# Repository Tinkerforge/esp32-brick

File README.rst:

ESP32 Brick
===========

This repository contains the firmware source code and the hardware design
files. The documentation generator configs can be found at
https://github.com/Tinkerforge/generators

Repository Overview
-------------------

.. DO NOT EDIT THIS OVERVIEW MANUALLY! CHANGE https://github.com/Tinkerforge/esp32-firmware/repo_overview.rst AND COPY THAT BLOCK INTO ALL REPOS LISTED BELOW. TODO: AUTOMATE THIS

Software
~~~~~~~~
- `esp32-firmware <https://github.com/Tinkerforge/esp32-firmware>`__  **Please report any issues concerning WARP hard- and software here!** Source code of the ESP32 firmware shared between all WARP Chargers and Energy Managers

- `tfjson <https://github.com/Tinkerforge/tfjson>`__ SAX style JSON serializer and deserializer
- `tfmodbustcp <https://github.com/Tinkerforge/tfmodbustcp>`__ Modbus TCP server and client implementation
- `tfocpp <https://github.com/Tinkerforge/tfocpp>`__ OCPP 1.6 implementation
- `tftools <https://github.com/Tinkerforge/tftools>`__ Miscellaneous tools and helpers

- `esp32-remote-access <https://github.com/Tinkerforge/esp32-remote-access>`__ Source code of the my.warp-charger.com remote access server

- `warp-charger <https://github.com/Tinkerforge/warp-charger>`__ The source code of (docs.)warp-charger.com and the printed manual, released firmwares, datasheets and documents, as well as some tools and hardware design files
- `api.warp-charger.com <https://github.com/Tinkerforge/api.warp-charger.com>`__ Serves APIs that are used by WARP Chargers to obtain relevant public information like day ahead prices
- `vislog.warp-charger.com <https://github.com/Tinkerforge/vislog.warp-charger.com>`__ Visualizes WARP Charger logs and EVSE debug protocols
- `dbus-warp-charger <https://github.com/Tinkerforge/dbus-warp-charger>`__ Integrates WARP Chargers into a Victron Energy Venus OS device (e.g. Cerbo GX)

WARP Charger Hardware
~~~~~~~~~~~~~~~~~~~~~~

- `esp32-brick <https://github.com/Tinkerforge/esp32-brick>`__ Hardware design files of the ESP32 Brick
- `evse-bricklet <https://github.com/Tinkerforge/evse-bricklet>`__  Firmware source code and hardware design files of the EVSE Bricklet
- `rs485-bricklet <https://github.com/Tinkerforge/rs485-bricklet>`__ Firmware source code and hardware design files of the RS485 Bricklet

WARP2 Charger Hardware
~~~~~~~~~~~~~~~~~~~~~~

- `esp32-ethernet-brick <https://github.com/Tinkerforge/esp32-ethernet-brick>`__ Hardware design files of the ESP32 Ethernet Brick
- `evse-v2-bricklet <https://github.com/Tinkerforge/evse-v2-bricklet>`__ Firmware source code and hardware design files of the EVSE 2.0 Bricklet
- `nfc-bricklet <https://github.com/Tinkerforge/nfc-bricklet>`__ Firmware source code and hardware design files of the NFC Bricklet

WARP3 Charger Hardware
~~~~~~~~~~~~~~~~~~~~~~

- `warp-esp32-ethernet-brick <https://github.com/Tinkerforge/warp-esp32-ethernet-brick>`__ Hardware design files of the WARP ESP32 Ethernet Brick
- `evse-v3-bricklet <https://github.com/Tinkerforge/evse-v3-bricklet>`__ Firmware source code and hardware design files of the EVSE 3.0 Bricklet
- `nfc-bricklet <https://github.com/Tinkerforge/nfc-bricklet>`__ Firmware source code and hardware design files of the NFC Bricklet

WARP Energy Manager Hardware
~~~~~~~~~~~~~~~~~~~~~~~~~~~~

- `esp32-ethernet-brick <https://github.com/Tinkerforge/esp32-ethernet-brick>`__ Hardware design files of the ESP32 Ethernet Brick
- `warp-energy-manager-bricklet <https://github.com/Tinkerforge/warp-energy-manager-bricklet>`__ Firmware source code and hardware design files of the WARP Energy Manager Bricklet

WARP Energy Manager 2.0 Hardware
~~~~~~~~~~~~~~~~~~~~~~~~~~~~~~~~

- `esp32-ethernet-brick <https://github.com/Tinkerforge/esp32-ethernet-brick>`__ Hardware design files of the ESP32 Ethernet Brick
- `warp-energy-manager-v2-bricklet <https://github.com/Tinkerforge/warp-energy-manager-v2-bricklet>`__ Firmware source code and hardware design files of the WARP Energy Manager 2.0 Bricklet
- `warp-front-panel-bricklet <https://github.com/Tinkerforge/warp-front-panel-bricklet>`__ Firmware source code and hardware design files of the WARP Front Panel Bricklet

Forked/patched projects
~~~~~~~~~~~~~~~~~~~~~~~

- `arduino-esp32 <https://github.com/Tinkerforge/arduino-esp32>`__
- `esp32-arduino-libs <https://github.com/Tinkerforge/esp32-arduino-libs>`__
- `WireGuard-ESP32-Arduino <https://github.com/Tinkerforge/WireGuard-ESP32-Arduino>`__

Repository Content
------------------

software/:
 * examples/: Examples for all supported languages
 * build/: Compiled files
 * src/: Source code of firmware
 * Makefile: Makefile to build project

hardware/:
 * Contains KiCad project files and additionally schematics as PDF

datasheets/:
 * Contains datasheets for sensors and complex ICs that are used

Hardware
--------

The hardware is designed with the open source EDA Suite KiCad
(http://www.kicad.org). Before you are able to open the files,
you have to install the Tinkerforge kicad-libraries
(https://github.com/Tinkerforge/kicad-libraries). You can either clone
them directly in hardware/ or clone them in a separate folder and
symlink them into hardware/
(ln -s kicad_path/kicad-libraries project_path/hardware). After that you
can open the .pro file in hardware/ with KiCad and from there view and
modify the schematics and the PCB layout.

Software
--------

See README.txt in the software folder for details.

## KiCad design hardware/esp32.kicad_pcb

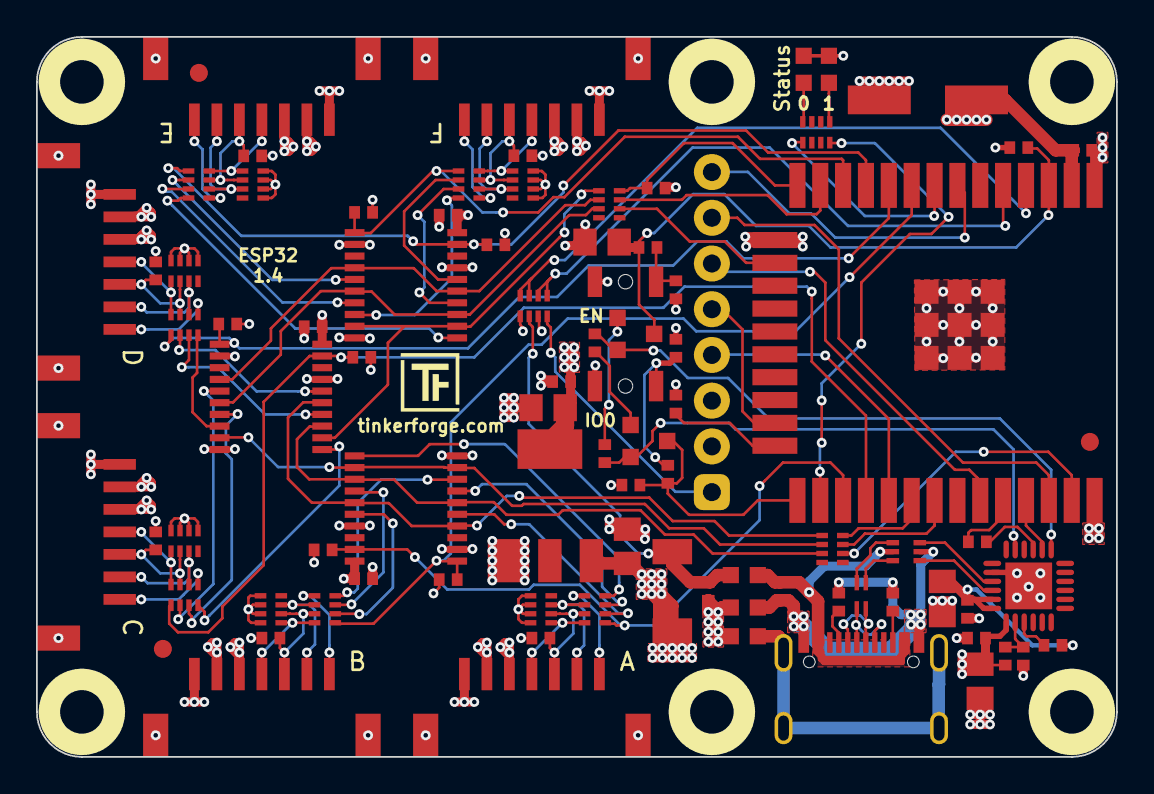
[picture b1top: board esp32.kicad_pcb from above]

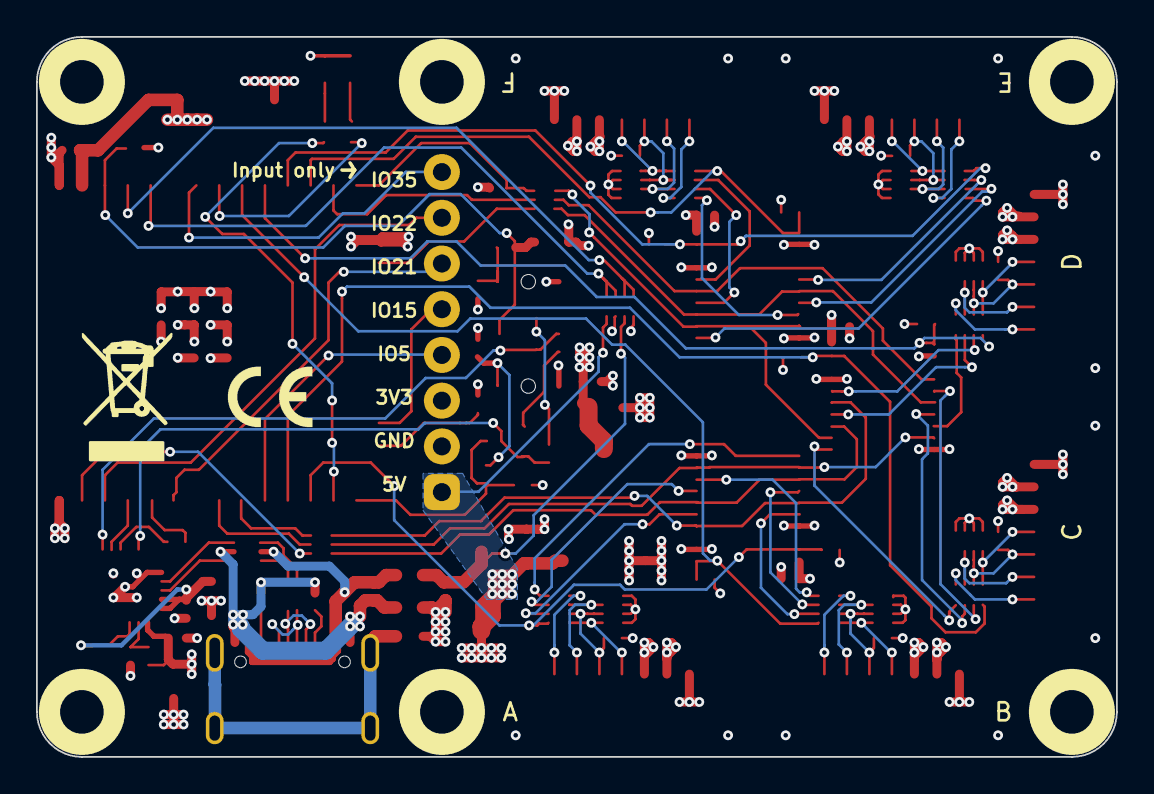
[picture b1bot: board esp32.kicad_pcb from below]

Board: 4 copper layers, 60.0 x 40.0 mm, 94 parts (2 on the bottom side), 101 nets.

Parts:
C101, C102: 1uF; C0402F
C103, C104, C108, C111: 4.7uF; C0805E
C105: 100uF; ELKO_63
C106, C107, C109, C110, C201, C202, C203: 100nF; C0402F
C112: 10µF; C0805E
C113, C114: 1nF; C0402F
CP201, CP202, CP203, CP204, CP205, CP206: 220pF; 4X0402
D101: blue; D0603F
D102: PMEG4050; SOD-128
D105: green; D0603F
F101, F102, F103, F104: DRILL; DRILL_NP
Fiducial_Mark: VAL**; Fiducial_Mark
Fiducial_Mark#2, Fiducial_Mark#3: VAL**; Fiducial_Mark
J101: USB-C-2
L101, L103, L104: FB; R0603F
L102: 744230900; WE-CNSW-0603
P101: EXT_HEADER; pin_array_1x8-P2mm_D1mm
P201, P202, P203, P204, P205, P206: CON-SENSOR2
Q101, Q102: BC817; SOT23EBC
R1, R2, R3, R4, R108, R109, R201, R202: 100k; R0402F
R101, R103: 5.1k; R0402F
R102, R112: DNP; R0402F
R104: 22k; R0402F
R105: 47k; R0402F
R106: 1k; R0402F
R107: 100; R0402F
R110, R111: 12k; R0402F
R113, R114: 470; R0402F
R203, R204, R205, R206, R207, R208: 10k; R0402F
RP101, RP102, RP201, RP202, RP203, RP204, RP205, RP206: 82; 4X0402
RP104, RP105: 1k; 4X0402
SW101, SW102: B3U-1000P
U101: 82400152; SOT563-SPEC
U102: AZ1117E-3.3V; SOT-223
U103: CP2102N-A02-GQFN24R; QFN24-4x4mm-0.5mm
U104: ESP32WRM32E128PH; ESP32-WROOM-32
U201, U202, U203: 74AHC244; TSSOP20
VAL: WEEE_7mm
VAL#2: CE_5mm

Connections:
3V3: C105.1, C106.2, C108.2, C109.2, C201.2, C202.2, C203.2, D101.1, D105.1, P101.3, P201.3, P202.3, P203.3, P204.3, P205.3, P206.3, R1.1, R2.1, R3.1, R4.1, R110.2, R111.1, R201.1, R202.1, R203.1, R204.1, R205.1, R206.1, R207.1, R208.1, U102.2, U104.2, U201.20, U202.20, U203.20
5V: C103.2, C104.2, C107.2, D102.2, P101.1, P201.1, P202.1, P203.1, P204.1, P205.1, P206.1, R104.2, RP104.8, U102.3, U103.7
B0-CLK: RP101.2, U201.4, U201.15, U202.4
B0-CS0: R203.2, RP201.1, U104.12, U201.1
B0-CS1: R205.2, RP202.1, U104.11, U201.19
B0-CS2: R204.2, RP203.1, U104.10, U202.1
B0-MISO: RP101.1, U201.9, U201.12, U202.12
B0-MOSI: RP101.3, U201.6, U201.13, U202.6
B1-CLK: RP102.1, U202.15, U203.4, U203.15
B1-CS0: R206.2, RP204.1, U104.28, U202.19
B1-CS1: R207.2, RP205.1, U104.9, U203.1
B1-CS2: R208.2, RP206.1, U104.27, U203.19
B1-MISO: RP102.2, U202.9, U203.9, U203.12
B1-MOSI: RP102.3, U202.13, U203.6, U203.13
ESP_ADC_5V: RP104.3, RP104.4, U104.4
ESP_ADC_VUSB: RP104.1, RP104.2, U104.5
ESP_EN: C112.2, Q101.C, R111.2, R113.2, U104.3
ESP_IO0: Q102.C, R110.1, R114.2, U104.25
ESP_IO2: R112.1, U104.24
ESP_IO5: P101.4, U104.29
ESP_IO15: P101.5, U104.23
ESP_IO21: P101.6, U104.33
ESP_IO22: P101.7, U104.36
ESP_IO35: P101.8, U104.7
ESP_RXD: R107.2, U104.34
ESP_TXD: U103.20, U104.35
GND: C101.1, C103.1, C104.1, C105.2, C106.1, C107.1, C108.1, C109.1, C110.1, C111.1, C112.1, C113.2, C114.2, C201.1, C202.1, C203.1, CP201.5, CP201.6, CP201.7, CP201.8, CP202.5, CP202.6, CP202.7, CP202.8, CP203.5, CP203.6, CP203.7, CP203.8, CP204.5, CP204.6, CP204.7, CP204.8, CP205.5, CP205.6, CP205.7, CP205.8, CP206.5, CP206.6, CP206.7, CP206.8, L101.1, L104.2, P101.2, P201.2, P201.EP, P202.2, P202.EP, P203.2, P203.EP, P204.2, P204.EP, P205.2, P205.EP, P206.2, P206.EP, R102.2, R105.1, R112.2, RP104.5, RP104.7, SW101.1, SW102.1, U102.1, U103.2, U103.EXP, U104.1, U104.15, U104.38, U104.39, U201.2, U201.10, U201.17, U202.2, U202.10, U202.17, U203.2, U203.10, U203.17
LED_BLUE: RP105.5, U104.8
LED_GREEN: RP105.8, U104.26
unnamed: C101.2, D102.1, L103.2, RP104.6
unnamed: C110.2, C111.2, R106.2, U103.5, U103.6
unnamed: C113.1, R113.1, SW101.2
unnamed: C114.1, R114.1, SW102.2
unnamed: CP201.1, P201.4, RP201.8
unnamed: CP201.2, P201.5, R1.2, RP201.7
unnamed: CP201.3, P201.6, RP201.6
unnamed: CP202.1, P202.4, RP202.8
unnamed: CP202.2, P202.5, R2.2, RP202.7
unnamed: CP202.3, P202.6, RP202.6
unnamed: CP203.1, P203.4, RP203.8
unnamed: CP203.2, P203.5, R3.2, RP203.7
unnamed: CP203.3, P203.6, RP203.6
unnamed: CP204.1, P204.4, RP204.8
unnamed: CP204.2, P204.5, R4.2, RP204.7
unnamed: CP204.3, P204.6, RP204.6
unnamed: CP205.1, P205.4, RP205.8
unnamed: CP205.2, P205.5, R201.2, RP205.7
unnamed: CP205.3, P205.6, RP205.6
unnamed: CP206.1, P206.4, RP206.8
unnamed: CP206.2, P206.5, R202.2, RP206.7
unnamed: CP206.3, P206.6, RP206.6
unnamed: D101.2, RP105.4
unnamed: D105.2, RP105.1
unnamed: J101.2, L102.2
unnamed: J101.3, L102.3
unnamed: J101.4, R101.2
unnamed: J101.5, R103.2
unnamed: J101.SHD, L101.2
unnamed: L102.1, U101.6
unnamed: L102.4, U101.4
unnamed: P201.7, RP201.5
unnamed: P202.7, RP202.5
unnamed: P203.7, RP203.5
unnamed: P204.7, RP204.5
unnamed: P205.7, RP205.5
unnamed: P206.7, RP206.5
unnamed: Q101.B, R108.2
unnamed: Q101.E, R109.1, U103.19
unnamed: Q102.B, R109.2
unnamed: Q102.E, R108.1, U103.23
unnamed: R102.1, RP101.8, U104.14
unnamed: R104.1, R105.2, U103.8
unnamed: R106.1, U103.9
unnamed: R107.1, U103.21
unnamed: RP101.6, U104.16
unnamed: RP101.7, U104.13
unnamed: RP102.6, U104.37
unnamed: RP102.7, U104.31
unnamed: RP102.8, U104.30
unnamed: RP201.2, U201.16
unnamed: RP201.3, U201.14
unnamed: RP201.4, U201.8
unnamed: RP202.2, U201.5
unnamed: RP202.3, U201.7
unnamed: RP202.4, U201.11
unnamed: RP203.2, U202.16
unnamed: RP203.3, U202.14
unnamed: RP203.4, U202.8
unnamed: RP204.2, U202.5
unnamed: RP204.3, U202.7
unnamed: RP204.4, U202.11
unnamed: RP205.2, U203.16
unnamed: RP205.3, U203.14
unnamed: RP205.4, U203.8
unnamed: RP206.2, U203.5
unnamed: RP206.3, U203.7
unnamed: RP206.4, U203.11
unnamed: U101.1, U103.4
unnamed: U101.3, U103.3
USB_5V: C102.2, J101.1, L103.1, U101.5
USB_GND: C102.1, J101.6, L104.1, R101.1, R103.1, U101.2

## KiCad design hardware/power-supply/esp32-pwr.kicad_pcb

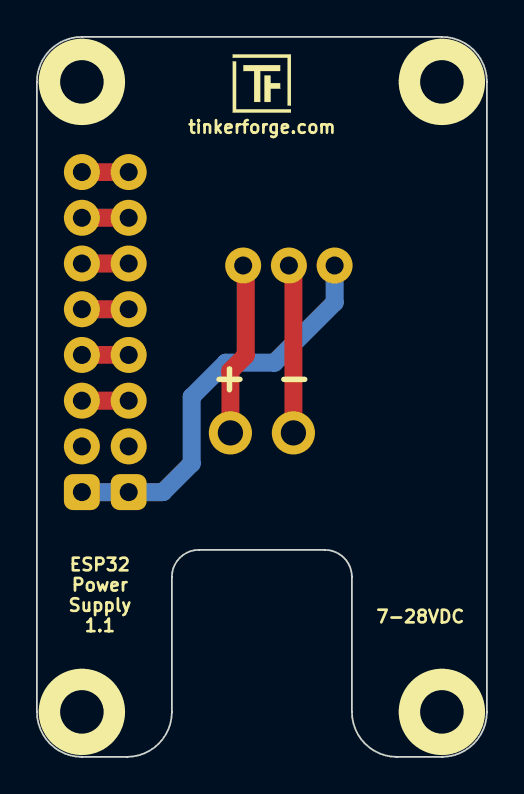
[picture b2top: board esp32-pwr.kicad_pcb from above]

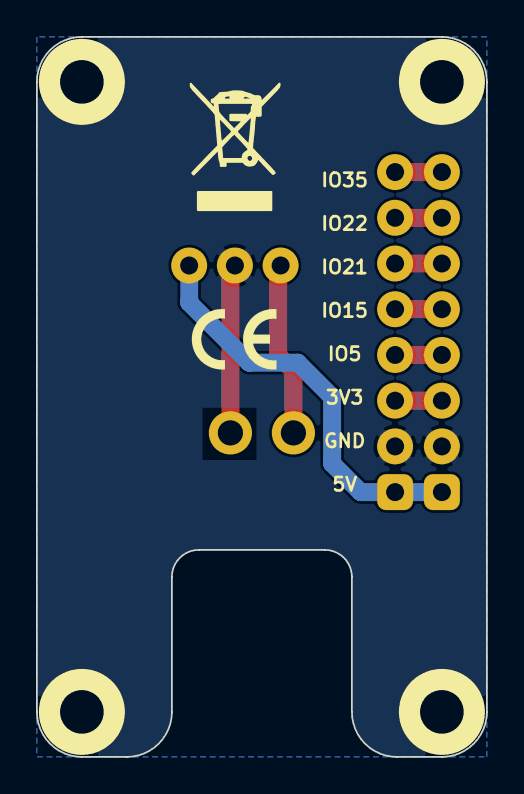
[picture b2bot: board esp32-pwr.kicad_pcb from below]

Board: 2 copper layers, 25.0 x 40.0 mm, 8 parts (2 on the bottom side), 9 nets.

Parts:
F103, F104: DRILL; DRILL_NP
P101, P103: EXT_HEADER; pin_array_1x8-P2mm_D1mm
P102: PWR IN; OQ_2P
U101: WPMDL1100501S; WPMDL110
VAL: CE_5mm
VAL#2: WEEE_7mm

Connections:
5V: P101.1, P103.1, U101.3
GND: P101.2, P102.2, P103.2, U101.2
unnamed: P101.3, P103.3
unnamed: P101.4, P103.4
unnamed: P101.5, P103.5
unnamed: P101.6, P103.6
unnamed: P101.7, P103.7
unnamed: P101.8, P103.8
unnamed: P102.1, U101.1

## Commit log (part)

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2020-04-17 add first parts of schematic and board
2020-04-20 routing finished
2020-04-24 specify diodes
2020-05-20 define parts
2020-05-20 bugfix flash circuitry
2020-08-04 esp brick version 1.1
    changed power input connector 2 pole
    fix npn cricuitry
2020-08-05 add larger header
2020-08-06 switch from 4 layer design to 2 layer
2020-08-14 updated footprints drc
2020-08-25 version 1.2
    * fix usb-c cc resistors
2020-09-09 fix vcc layer
2020-09-10 fix values
2020-09-11 add push buttons
2020-09-24 Changed values of R108 and R109 from 12k to 100k Changed value of R110 form 5k to 12k
2020-10-20 added fcstd
2020-12-02 Add first firmware version.
2020-12-08 Handle missing passphrase input for unencrypted wifi networks.
2020-12-09 Don't create base58 strings with leading 1s.
    The base58 1 maps to 0, so leading 1s will be removed when decoding
    and then reencoding.
2020-12-10 Don't use sed to patch the web interface array header.
    This circumvents problems with BSD sed and the -i flag.
2020-12-13 Bump ini from 1.3.5 to 1.3.8 in /software/web
    Bumps [ini](https://github.com/isaacs/ini) from 1.3.5 to 1.3.8.
    - [Release notes](https://github.com/isaacs/ini/releases)
    - [Commits](https://github.com/isaacs/ini/compare/v1.3.5...v1.3.8)
2020-12-22 add version 1.4
    * add CS 10k resistors to SPI
    * fix logo positions
2021-01-11 Add support for translations. Add german translation.
2021-01-11 Track config updates.
2021-01-11 Fix firmware update label in fallback page.
2021-01-13 mqtt: Don't connect if not initialized.
2021-01-13 config: Support partial upgrades.
2021-01-13 Fix some translations.
2021-01-15 label: Allow warp as SSID prefix
2021-01-15 mqtt: Add missing translations.
2021-01-15 mqtt: Try to connect to broker every 5 seconds.
2021-01-15 Add debug module.
2021-01-15 Make MQTT connection trigger more robust.
2021-01-19 label: Don't assume that CWD is script home
2021-01-19 Add provisioning script.
2021-01-19 label: Fix darkness setting
2021-01-20 wifi: Improve access point mode selection strings.
2021-01-20 Fine-tune layout and translations.
2021-01-20 wifi: De-cardify static IP configuration.
2021-01-21 Add current date and time to debug report filename.
2021-01-21 Fine-tune form validation and translations.
2021-01-21 Fix provisioning script.
2021-01-28 Rework API. Use module prefixes with /, not _. Extend debug report.
2021-01-29 wifi: Flatten wifi scan results.
2021-01-29 firmware_update: Block updates if requested by other module.
2021-01-29 wifi: Restore printing the STA IP on the serial console.
2021-02-01 api: Fix race condition in onMqttConnect.
    onMqttConnect happens asynchronously to the
    "main thread" i.e. the one used by the task scheduler.
    This enabled a race condition between the MQTT publishing when
    a client (re)connects and the publishing when a state changes.
2021-02-02 Add event log.
2021-02-03 fix port bottom descriptions
2021-02-10 mqtt: Don't try to connect if Wifi is currently reconnecting.
2021-02-10 Update provisioning scripts.
2021-02-10 provisioning: Polish.
2021-02-11 provisioning: Explicitly check if the expected bricklets are there.
2021-02-11 mqtt, wifi: Fix passphrase invalid bug on successful save.
2021-02-16 wifi, mqtt: Add RSSI staus. Drop "connected to" from status.
2021-02-16 mqtt: Add description to error codes.
2021-02-16 provisioning: Fix printing of non-str values
2021-02-17 wifi: Fix passphrase print alignment.
2021-02-17 Add keep-alive event. Reconnect on event loss. Reload on reboot.
2021-02-24 Fine-tune translations.
2021-02-24 Rework WiFi and MQTT connection handling. Use QoS 0.
2021-02-26 Add license.
2021-03-02 provisioning: Check ESP fuses with QR code. Add install instructions.
2021-03-04 mqtt: Improve logging. Always unsubscribe before (re-)subscribing.
2021-03-05 Fix spacing between navbar symbols and links.
2021-03-05 Remove onEventConnect.
2021-03-11 add readme
2021-03-12 authentication: Add custom login page. Remove logout button.
    Logging out a user by overwriting the cached credentials only works
    in Chrome up to version 78 and in Firefox. The cache is cleared when
    closing the browser window anyway, so this is unnecessary confusing.
2021-03-12 Update translations.
2021-03-16 wifi: Don't leak passphase to serial console.
2021-03-16 authentication: Fix typo.
2021-03-19 wifi: Add sta_bssid to state.
2021-03-19 wifi: Show BSSID if SSID is ambiguous. Prefill BSSID lock.
    SSIDs are ambiguous if multiple APs are available (e.g. with repeaters)
    If the RSSI of multiple APs differs by at least 15, prefill the
    BSSID lock to make sure, that we always connect to the AP with the
    best reception.
2021-03-19 Use util.passwordUpdate.
2021-03-19 firmware_update: Reboot faster after updates.
2021-03-22 Update javascript dependencies.
2021-03-26 provisioning: Add "basic" support. Auto-download firmwares.
2021-03-29 provisioning: Add shebang line
2021-03-31 provisioning: Add docket support
2021-04-08 add somehow missing logos and fiducials
2021-04-13 provisioning: Verify burned eFuses.
2021-04-14 Fix syntax error
2021-04-15 wifi: Don't start a new scan if one is already running.
2021-04-15 wifi: Send event when wifi scan is done. Use event for web interface.
2021-04-15 provisioning: Change prompt to red if first scanned value is invalid.
2021-04-16 provisioning: Reflash test firmware if ESP proxy is not reachable.
2021-04-30 provisioning: Pull repo if no matching EVSE test report is found.
2021-05-03 authentication: Migrate login page to (dart-)sass.
2021-05-07 auth, mqtt, wifi: Use API::restorePersistantConfig.
2021-05-11 proxy: Add missing ConfArray parameters.
    The upper bound is required so that json_size
    calculates a correct size.
2021-05-18 provisioning: Update EVSE bindings.
2021-05-18 provisioning: Increase wifi timeout to 120 seconds.
2021-05-20 wifi: Port to arduino-esp 2.0 API.
2021-05-20 provisioning: Split into stage 0 and stage 1.
    Run stage 0 with
    parallel -j 9 -u python3 provision_stage_0.py [firmware] '{}' ::: /dev/ttyUSB*
    to flash up to nine ESPs in parallel. Then wait until the LEDs start
    blinking.
2021-05-28 Switch from printer hostname to IP address to avoid collision
2021-06-01 provisioning: Hard code static IP of label printer.
2021-06-07 authentication: Add config validation. Rework form.
2021-06-08 Improve english translation.
2021-06-10 authentication, web: Use python3.
2021-06-17 Add hidden proxy used for provisioning tests.
2021-06-21 provisioning: Add restore_wifi.py
2021-07-02 provisioning: Wait for input on exceptions/exits.
2021-07-07 provisioning: Don't pull git as root.
2021-07-19 debug: Remove unused code.
2021-07-19 mqtt: Only register as backend if MQTT is enabled.
2021-07-19 Port to new web server. Authentication does not work yet.
2021-07-23 web: Use util.add/remove_alert.
2021-07-27 wifi: Remove hard dependency to web socket module.
2021-07-30 http, mqtt: Use API::getCommmandBlockedReason.
2021-07-30 ethernet/wifi: Port to arduino-esp 2.0 API.
2021-07-30 Add prototype of ethernet module.
    Ethernet works, but has no configuration or web interface plugin yet.
2021-08-10 Add board modules with HALs. Use for firmware update.
2021-08-24 Fix form labels.
2021-08-25 ethernet: Fix connection state constants.
2021-08-25 wifi: Don't switch off if AP is closed. Currently broken.
    Calling wifi.softAPdisconnect(true) prints
    E wifi_init_default: esp_wifi_get_mac failed with 12289
    This seems to be this issue:
    https://github.com/espressif/arduino-esp32/issues/5459
2021-08-30 label: Add WARP2 support
2021-09-01 provisioning: Use consistent error reporting.
2021-09-01 hidden_proxy: Blink green status LED while running.
    This is primarily to check if the green LED is working while
    provisioning an ESP32 Ethernet Brick.
2021-09-07 Add initial stage 3 provisioning script
2021-09-08 wifi: Disable modem sleep to improve responsiveness.
    With modem sleep:
    200 packets transmitted, 200 received, 0% packet loss, time 199299ms
    rtt min/avg/max/mdev = 4.090/68.358/244.670/37.841 ms
    Without modem sleep:
    200 packets transmitted, 200 received, 0% packet loss, time 199297ms
    rtt min/avg/max/mdev = 2.720/14.280/65.018/10.458 ms
2021-09-08 provisioning: Don't assume USB cable is plugged.
2021-09-08 provisioning: Fix stage 2.
2021-09-08 provision: Run stage 2 in try except to show errors.
2021-09-08 provision: Ignore flash errors in stage 0. Add printer IP to stage 1.
2021-09-08 provisioning: Do a clean exit(0) if the printer is missing and the user aborts
    There's no point in reporting the full traceback in this case.
2021-09-08 provisioning: Mark more scripts as executable
2021-09-08 provisioning/stage1: Fix infinite loop
2021-09-08 provisioning: Don't report full traceback for fatal_error calls
    The fatal error is already handled by the caller of the fatal_error
    function. Only report tracebacks for unhandled exceptions.
2021-09-08 provisioing: Make FatalError behave the same way as SystemExit
2021-09-09 provision: Open web interface when done with stage 1.
2021-09-09 provisioning: Remove IO0 button test.
2021-09-10 provisioning/stage3: Add support for NFC and Color Bricklet
2021-09-10 provisioning/stage3: Add wallbox test function dummy
2021-09-10 provisioning/stage3: Add actual wallboxc test
2021-09-10 provisioning/stage3: Print test steps
2021-09-10 provision: Use automated tester in stage 2.
2021-09-10 provisioning: Fix return type
2021-09-10 provisioning: Green is for user interactions
2021-09-10 provisioning: Fix parameter name
2021-09-10 provisioning: Fix tag data access
2021-09-10 provisioning: Fix front panel button test logic
2021-09-13 provisioning/stage2: Use selenium to open web interface.
2021-09-13 provisioning: Prefer time.monotonic over time.time
2021-09-13 provisioning: Fine tune voltage measurement
2021-09-13 provisioning: Fix NFC tag blink logic
2021-09-13 provisioning: Add more prints to wallbox test
2021-09-13 provisioning: Indicate number of NFC tags to scan by blink position instead of color
2021-09-14 provisioning/stage_2: Test NFC.
2021-09-14 provisioning/common: Remove unnecesary fields from Enum tuple.
    This fixes duplicated enumerations, because those had
    different enumeration types.
2021-09-14 provisioning: Wait for integration time after releasing the button
2021-09-14 provisioning: Reorder some prints
2021-09-15 provisioning: Include electrical tests result in stage 2 report
2021-09-21 provisioning: No need to pass git user anymore
    Script is not run as root anymore.
2021-09-24 provisioning/stage3: Ensure that IEC states are stable
2021-09-30 provisioning/stage3: Add beep indicator for success/failure
2021-10-04 proxy: Port to new web server.
2021-10-06 provisioning/stage2: Improve meter error messages.
2021-10-07 wifi: Also force AP off on start-up.
2021-10-13 provisioning/stage1: Add timeout to reboot request.
2021-10-15 hidden_proxy: Remove unused code.
2021-10-18 authentication: Make sure node deps are installed.
2021-10-20 provisioning/warp2: Switch from PyQt5 to tk
    To avoid strange conflict between OpenCV and PyQt5.
2021-10-22 event_log: Merge download event log and debug report buttons.
2021-10-25 event_log: Redesign sub-page layout.
2021-10-27 event_log: Update translations.
2021-10-29 ethernet: Notify API when connected.
2021-10-29 wifi: Remove api.reconnectDone usage.
2021-10-29 mqtt: Add missing declaration.
2021-11-04 provisioning/stage2: Add hint why proxy connection could be failed.
2021-11-04 provisioning/common: Fix imports.
2021-11-04 provisioning/stage2: Update firmware if outdated.
2021-11-11 provisioning: Fix typo in eFuse check error message
2021-11-12 provision/stage_2: Fix error handling.
2021-11-12 Fix typo
2021-11-12 wifi: Fix wifi state start value.
2021-11-12 esp32_brick, esp32_ethernet_brick: Use Brick HALs.
2021-11-12 mqtt: Fix format parameter.
2022-01-31 add schematic
2022-04-01 add 3d files

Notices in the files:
hardware/esp32.kicad_pcb:
Licensed under CERN OHL v.1.1
Copyright (©) 2020, B.Nordmeyer
Copyright Tinkerforge GmbH 2020.
This documentation describes Open Hardware and is licensed under the
CERN OHL v. 1.1.
